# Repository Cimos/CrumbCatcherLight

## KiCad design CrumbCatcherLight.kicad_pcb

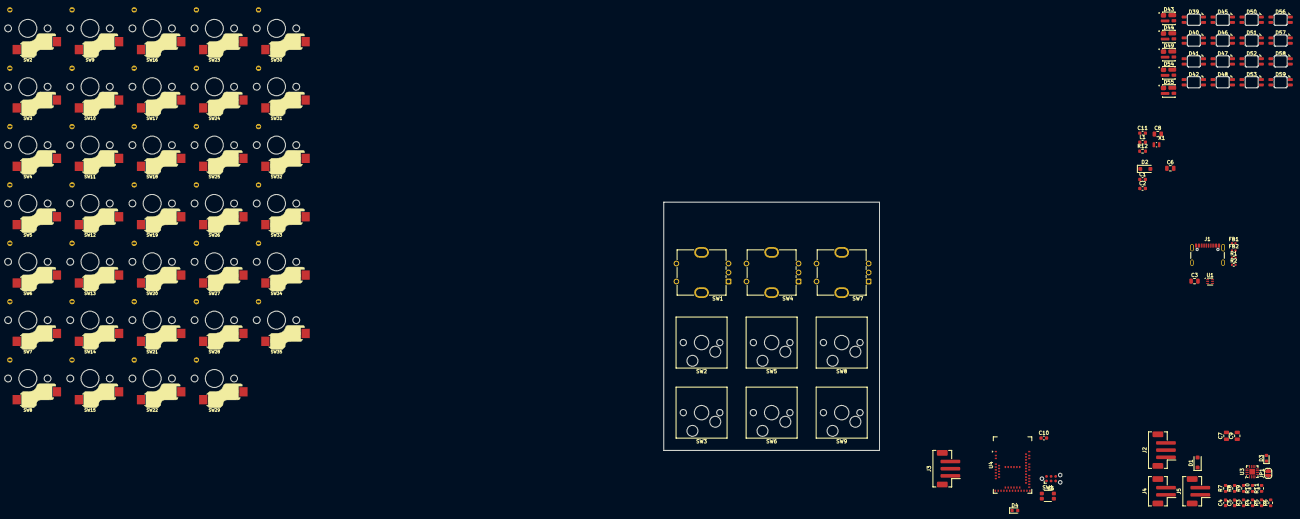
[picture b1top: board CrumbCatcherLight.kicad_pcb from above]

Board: 2 copper layers, 107 parts (0 on the bottom side), 69 nets, no tracks yet.

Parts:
C1, C2, C5: 100nF; C_0603_1608Metric
C3, C6, C7, C8, C9: 10uF; C_0805_2012Metric
C4: 1uF; C_0603_1608Metric
C10, C11: 12pF; C_0603_1608Metric
D1, D2: MBR120VL; D_SOD-123F
D3: Yellow; LED_0603_1608Metric
D4: GREEN; LED_0603_1608Metric
D39, D40, D41, D42, D45, D46, D47, D48, D50, D51, D52, D53, D56, D57, D58, D59: SK6812_MINI_E; SK6812MINI-E
D43, D44, D49, D54, D55: SK6812MINI; SK6812MINI-012
FB1, FB2: BLM15PX330SN1D; L_0402_1005Metric
J1: USB_C_Receptacle; USB_C_Receptacle_GCT_USB4105-xx-A_16P_TopMnt_Horizontal
J2: Qi Charger In; JST_PH_B3B-PH-SM4-TB_1x03-1MP_P2.00mm_Vertical
J3: Battery with NTC; JST_PH_B3B-PH-SM4-TB_1x03-1MP_P2.00mm_Vertical
J4: Battery No NTC; JST_PH_B2B-PH-SM4-TB_1x02-1MP_P2.00mm_Vertical
J5: NTC; JST_PH_B2B-PH-SM4-TB_1x02-1MP_P2.00mm_Vertical
J6: Conn_ARM_SWD_TagConnect_TC2030-NL; Tag-Connect_TC2030-IDC-NL_2x03_P1.27mm_Vertical
JP1: Charge Boost; SolderJumper-2_P1.3mm_Open_RoundedPad1.0x1.5mm
L1: 10uH; L_0603_1608Metric
R1, R2: 5K1; R_0402_1005Metric
R3, R4, R5, R6, R12: 1K; R_0603_1608Metric
R7, R8, R11: 10K; R_0603_1608Metric
R9: 806k; R_0603_1608Metric
R10: 2M; R_0603_1608Metric
SW1, SW4, SW7#2: PEC11R; RotaryEncoder_Bourns_Vertical_PEC12R-3x17F-Sxxxx
SW1#2: EVPAA202K; EVP-AA202K
SW2, SW3, SW5#2, SW6, SW8#2, SW9: SW_SPST; SW_Hotswap_Kailh_MX_1.00u
SW2#2, SW3#2, SW4#2, SW5, SW6#2, SW7, SW8, SW9#2, SW10, SW11, SW12, SW13, SW14, SW15, SW16, SW17, SW18, SW19, SW20, SW21, SW22, SW23, SW24, SW25, SW26, SW27, SW28, SW29, SW30, SW31, SW32, SW33, SW34, SW35: SW_SPST; keyswitch_choc12_hotswap_1u
U1: ECMF02-2AMX6; ST_UQFN-6L_1.5x1.7mm_P0.5mm
U2: PCB; BOM
U3: BQ24075RGT; VQFN-16-1EP_3x3mm_P0.5mm_EP1.6x1.6mm
U4: MDBT50Q-U1MV2; Raytac_MDBT50Q
X1: 32.768kHz; XTAL_FC-12M

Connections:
+5V: C2.1, C3.1, C4.2, C5.1, C8.2, D1.1 (K), D1.2 (A), D2.1 (K), J2.1, U3.13 (IN), U4.32 (VBUS)
+VBATT: J3.1, J4.1, R9.2, U3.2 (BAT), U3.3 (BAT)
/BATT_TS: J3.2, J5.1, R11.1, U3.1 (TS)
/BVOLT: R9.1, R10.2
/PreFIlterGND: C1.2, FB2.1, J1.A1 (GND), J1.A12 (GND), J1.B1 (GND), J1.B12 (GND), J1.S1 (SHIELD), R1.2, R2.2, U1.3 (GND)
/Switches/Col0: SW1.S1, SW2.2 (B), SW3.2 (B)
/Switches/Col1: SW4.S1, SW5#2.2 (B), SW6.2 (B)
/Switches/Col2: SW7#2.S1, SW8#2.2 (B), SW9.2 (B)
/Untitled Sheet/+5V: D39.1 (VDD), D40.1 (VDD), D41.1 (VDD), D42.1 (VDD), D43.2 (VDD), D44.2 (VDD), D45.1 (VDD), D46.1 (VDD), D47.1 (VDD), D48.1 (VDD), D49.2 (VDD), D50.1 (VDD), D51.1 (VDD), D52.1 (VDD), D53.1 (VDD), D54.2 (VDD), D55.2 (VDD), D56.1 (VDD), D57.1 (VDD), D58.1 (VDD), D59.1 (VDD)
/Untitled Sheet/Col0: SW2#2.2 (B), SW3#2.2 (B), SW4#2.2 (B), SW5.2 (B), SW6#2.2 (B)
/Untitled Sheet/Col1: SW7.2 (B), SW8.2 (B), SW9#2.2 (B), SW10.2 (B), SW11.2 (B)
/Untitled Sheet/Col2: SW12.2 (B), SW13.2 (B), SW14.2 (B), SW15.2 (B), SW16.2 (B), SW17.2 (B)
/Untitled Sheet/Col3: SW18.2 (B), SW19.2 (B), SW20.2 (B), SW21.2 (B), SW22.2 (B), SW23.2 (B)
/Untitled Sheet/Col4: SW24.2 (B), SW25.2 (B), SW26.2 (B), SW27.2 (B), SW28.2 (B), SW29.2 (B)
/Untitled Sheet/Col5: SW30.2 (B), SW31.2 (B), SW32.2 (B), SW33.2 (B), SW34.2 (B), SW35.2 (B)
/Untitled Sheet/GND: D39.3 (GND), D40.3 (GND), D41.3 (GND), D42.3 (GND), D43.4 (GND), D44.4 (GND), D45.3 (GND), D46.3 (GND), D47.3 (GND), D48.3 (GND), D49.4 (GND), D50.3 (GND), D51.3 (GND), D52.3 (GND), D53.3 (GND), D54.4 (GND), D55.4 (GND), D56.3 (GND), D57.3 (GND), D58.3 (GND), D59.3 (GND)
/nRF52840/BLED: R12.2, U4.19 (P0.26)
/nRF52840/SWCLK: J6.4 (SWCLK), U4.53 (SWDCLK)
/nRF52840/SWDIO: J6.2 (SWDIO), U4.51 (SWDIO)
/nRF52840/USB_D_N: U1.6 (D+_out), U4.34 (D-)
/nRF52840/USB_D_P: U1.5 (D-_out), U4.35 (D+)
/nRF52840/~RST: J6.3 (~RESET), SW1#2.1, U4.40 (P0.18/~RST)
GND: C2.2, C3.2, C4.1, C5.2, C6.2, C7.1, C8.1, C9.1, C10.2, C11.2, D4.1 (K), FB2.2, J2.2, J3.3, J3.MP (MountPin), J4.2, J4.MP (MountPin), J5.2, J5.MP (MountPin), J6.5 (GND), R3.1, R4.1, R6.1, R7.2, R10.1, R11.2, SW1.C, SW1#2.2, SW4.C, SW7#2.C, U3.4 (~CE), U3.5 (EN2), U3.8 (VSS), U3.15 (SYSOFF), U3.17 (VSS), U4.1 (GND), U4.2 (GND), U4.15 (GND), U4.33 (GND), U4.55 (GND)
unnamed: D2.2 (A), FB1.2
unnamed: D3.2 (A), R8.2, SW2.1 (A)
unnamed: D3.1 (K), U3.9 (~CHG)
unnamed: D4.2 (A), R12.1, SW3.1 (A)
unnamed: SW1.S2, SW4#2.1 (A)
unnamed: SW5.1 (A), SW6.1 (A)
unnamed: SW5#2.1 (A), SW6#2.1 (A)
unnamed: SW4.S2, SW9#2.1 (A)
unnamed: SW8#2.1 (A), SW10.1 (A)
unnamed: SW9.1 (A), SW11.1 (A)
unnamed: SW7#2.S2, SW14.1 (A)
unnamed: D39.2 (DOUT), D40.4 (DIN)
unnamed: D40.2 (DOUT), D41.4 (DIN)
unnamed: D41.2 (DOUT), D42.4 (DIN)
unnamed: D42.2 (DOUT), D48.4 (DIN)
unnamed: D43.1 (DIN), D56.2 (DOUT)
unnamed: D43.3 (DOUT), D54.1 (DIN)
unnamed: D44.1 (DIN), D49.3 (DOUT)
unnamed: D44.3 (DOUT), D55.1 (DIN)
unnamed: D45.4 (DIN), D46.2 (DOUT)
unnamed: D45.2 (DOUT), D50.4 (DIN)
unnamed: D46.4 (DIN), D47.2 (DOUT)
unnamed: D47.4 (DIN), D48.2 (DOUT)
unnamed: D49.1 (DIN), D54.3 (DOUT)
unnamed: D50.2 (DOUT), D51.4 (DIN)
unnamed: D51.2 (DOUT), D52.4 (DIN)
unnamed: D52.2 (DOUT), D53.4 (DIN)
unnamed: D53.2 (DOUT), D59.4 (DIN)
unnamed: D56.4 (DIN), D57.2 (DOUT)
unnamed: D57.4 (DIN), D58.2 (DOUT)
unnamed: D58.4 (DIN), D59.2 (DOUT)
unnamed: J1.A5 (CC1), R1.1
unnamed: J1.B5 (CC2), R2.1
unnamed: JP1.1 (A), R7.1, U3.16 (ISET)
unnamed: JP1.2 (B), R5.2
unnamed: R5.1, R6.2
unnamed: J1.A7 (D-), J1.B7 (D-), U1.1 (D+_in)
unnamed: J1.A6 (D+), J1.B6 (D+), U1.2 (D-_in)
unnamed: R4.2, U3.12 (ILIM)
unnamed: R3.2, U3.14 (TMR)
unnamed: L1.2, U4.31 (DCCH)
unnamed: C10.1, U4.17 (P0.00/XL1), X1.2
unnamed: C11.1, U4.18 (P0.01/XL2), X1.1
unnamed: C9.2, L1.1, U4.28 (VDD)
VBUS: C1.1, FB1.1, J1.A4 (VBUS), J1.A9 (VBUS), J1.B4 (VBUS), J1.B9 (VBUS)
VDDH: C6.1, C7.2, R8.1, U3.6 (EN1), U3.10 (OUT), U3.11 (OUT), U4.30 (VDDH)

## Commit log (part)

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2023-10-23 Initial Project files commit
2023-10-24 Add MCU, remove teensy, separate sections into sheets
2023-10-25 Add stm crystal, update title block, add power on LED for 3V3 line
2024-03-16 Cleanup, Add usb emc and esd
2024-03-17 Update BOM, start to fill in part metadata
2024-03-19 Add LDO and other minor updates
    LP38691
2024-03-19 add mad_lib to project
2024-03-19 Project cleanup
2024-03-19 Add RP2040 to mad_lib
2024-03-22 Start component selection
2024-03-22 Select last few components, add and cleanup footprints
2024-03-23 Update lib, finish off rotary encoder schematic, reselect diode for reset circuit
    Update RP2040, rename bom only footprint, add mechanical footprint. Add PCB symbol
2024-03-24 Finish off rotary encoders, add EMC zone for USB, fix few remaining lib links, fix DRC
2024-03-26 add footprint for flash and 3d model
2024-08-04 Refactor, cleanup, add todo list, update metadata on BOM
2024-08-06 Update BOM,
2024-08-07 configure kibot
2024-08-07 update madlib, add todo
2024-08-08 Use .yaml file extension, add `submodules: recursive` to main repo checkout
2024-08-08 Generate change to create build
2024-08-08 Point to actual schematic sheet
2024-08-08 Clear ERC's
2024-08-08 update workflow to v4
2025-11-21 Add some reference circuits, add bq240xx, start to addnRF52840
2025-11-22 Update to nRF52840 module, add BQ for battery charging
2025-11-24 Split out BQ to own sheet
2025-11-24 More research, added connector for Qi charger in
2025-11-25 Add some todo notes, add 3/2 pin battery connectors
    Add NTC connector, Update power scheme for RF module
2025-11-26 Update BOM
2025-11-30 Add some research, update switches
